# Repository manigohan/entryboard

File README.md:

# entryboard
Turn your old phone into a ("SBC") easily!

# Licensing
This project is licensed under the TAPR OHL. See the [license file](LICENSE) or, http://www.tapr.org/OHL

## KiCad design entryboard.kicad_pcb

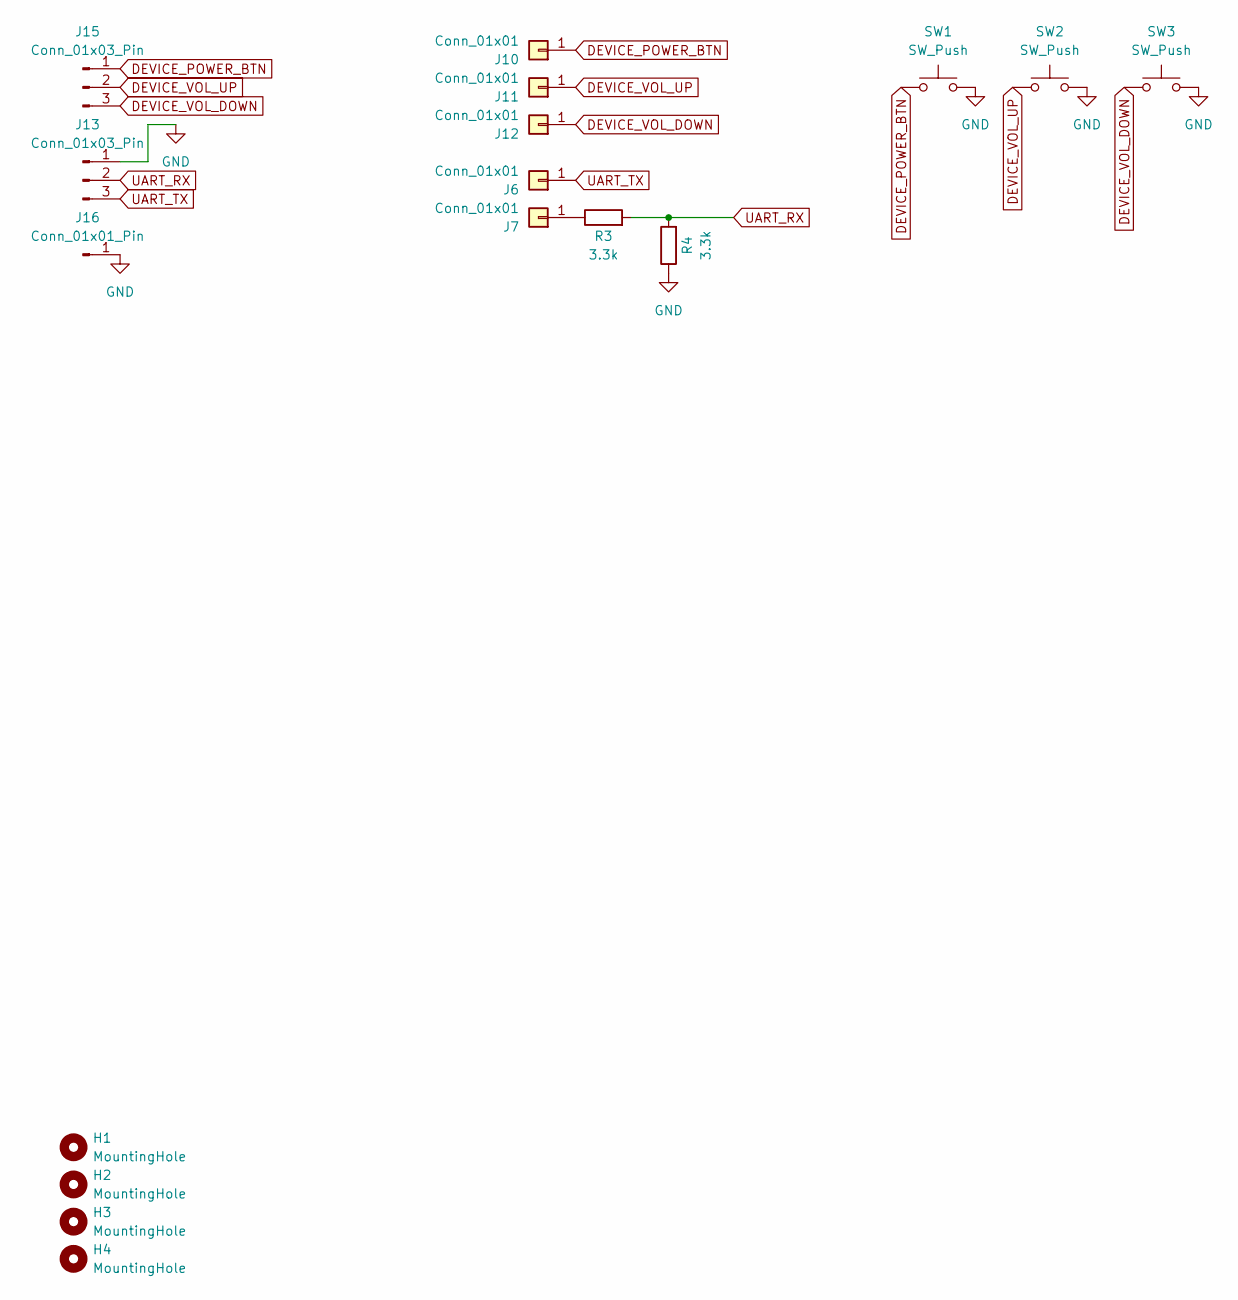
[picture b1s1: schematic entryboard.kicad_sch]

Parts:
H1, H2, H3, H4: MountingHole; MountingHole_2.5mm
J6, J7: Conn_01x01; TestPoint_Pad_1.0x1.0mm
J10, J11, J12: Conn_01x01; PinSocket_1x01_P2.54mm_Vertical
J13, J15: Conn_01x03_Pin; PinHeader_1x03_P2.54mm_Vertical
J16: Conn_01x01_Pin; PinHeader_1x01_P2.54mm_Vertical
R3, R4: 3.3k; R_1206_3216Metric_Pad1.30x1.75mm_HandSolder
SW1, SW2, SW3: SW_Push; SW_PUSH_6mm

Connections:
DEVICE_POWER_BTN: J10.1, J15.1, SW1.1
DEVICE_VOL_DOWN: J12.1, J15.3, SW3.1
DEVICE_VOL_UP: J11.1, J15.2, SW2.1
GND: J13.1, J16.1, R4.1, SW1.2, SW2.2, SW3.2
unnamed: J7.1, R3.1
UART_RX: J13.2, R3.2, R4.2
UART_TX: J6.1, J13.3

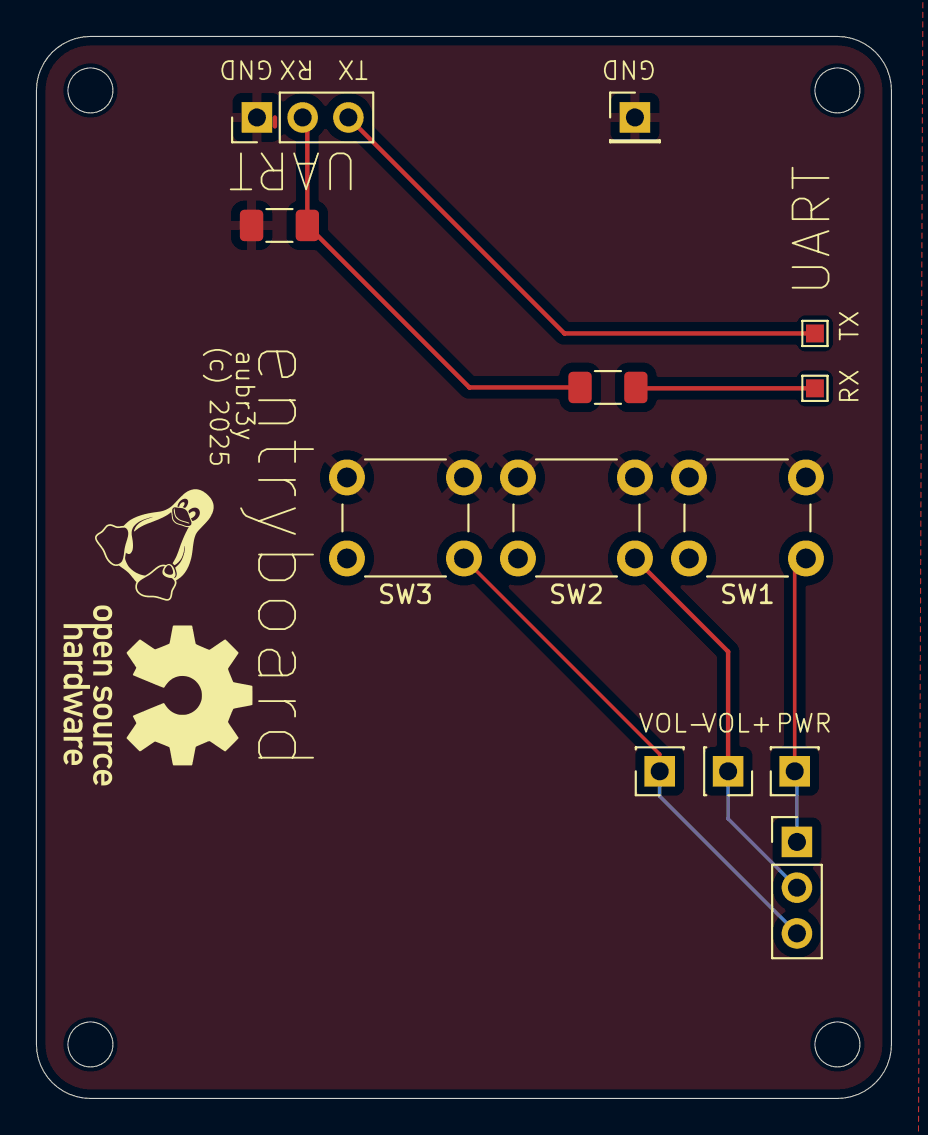
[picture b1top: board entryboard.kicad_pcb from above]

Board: 2 copper layers, 47.5 x 59.0 mm, 17 parts (0 on the bottom side), 7 nets.

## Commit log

2025-07-05 entryboard v1
2025-07-05 doc: Add TAPR License
2025-07-05 feat: add headers for keys, and another ground point
2025-07-05 doc: initial README stub
2025-07-05 doc: Add BoM
2025-07-05 fix: Use 2.54mm pitch header pins
2025-07-05 too much to say
2025-07-05 refactor: drop usbs, smaller board
2025-07-05 fix: make oshw farther from edge

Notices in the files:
entryboard.kicad_pcb:
(c) 2025
